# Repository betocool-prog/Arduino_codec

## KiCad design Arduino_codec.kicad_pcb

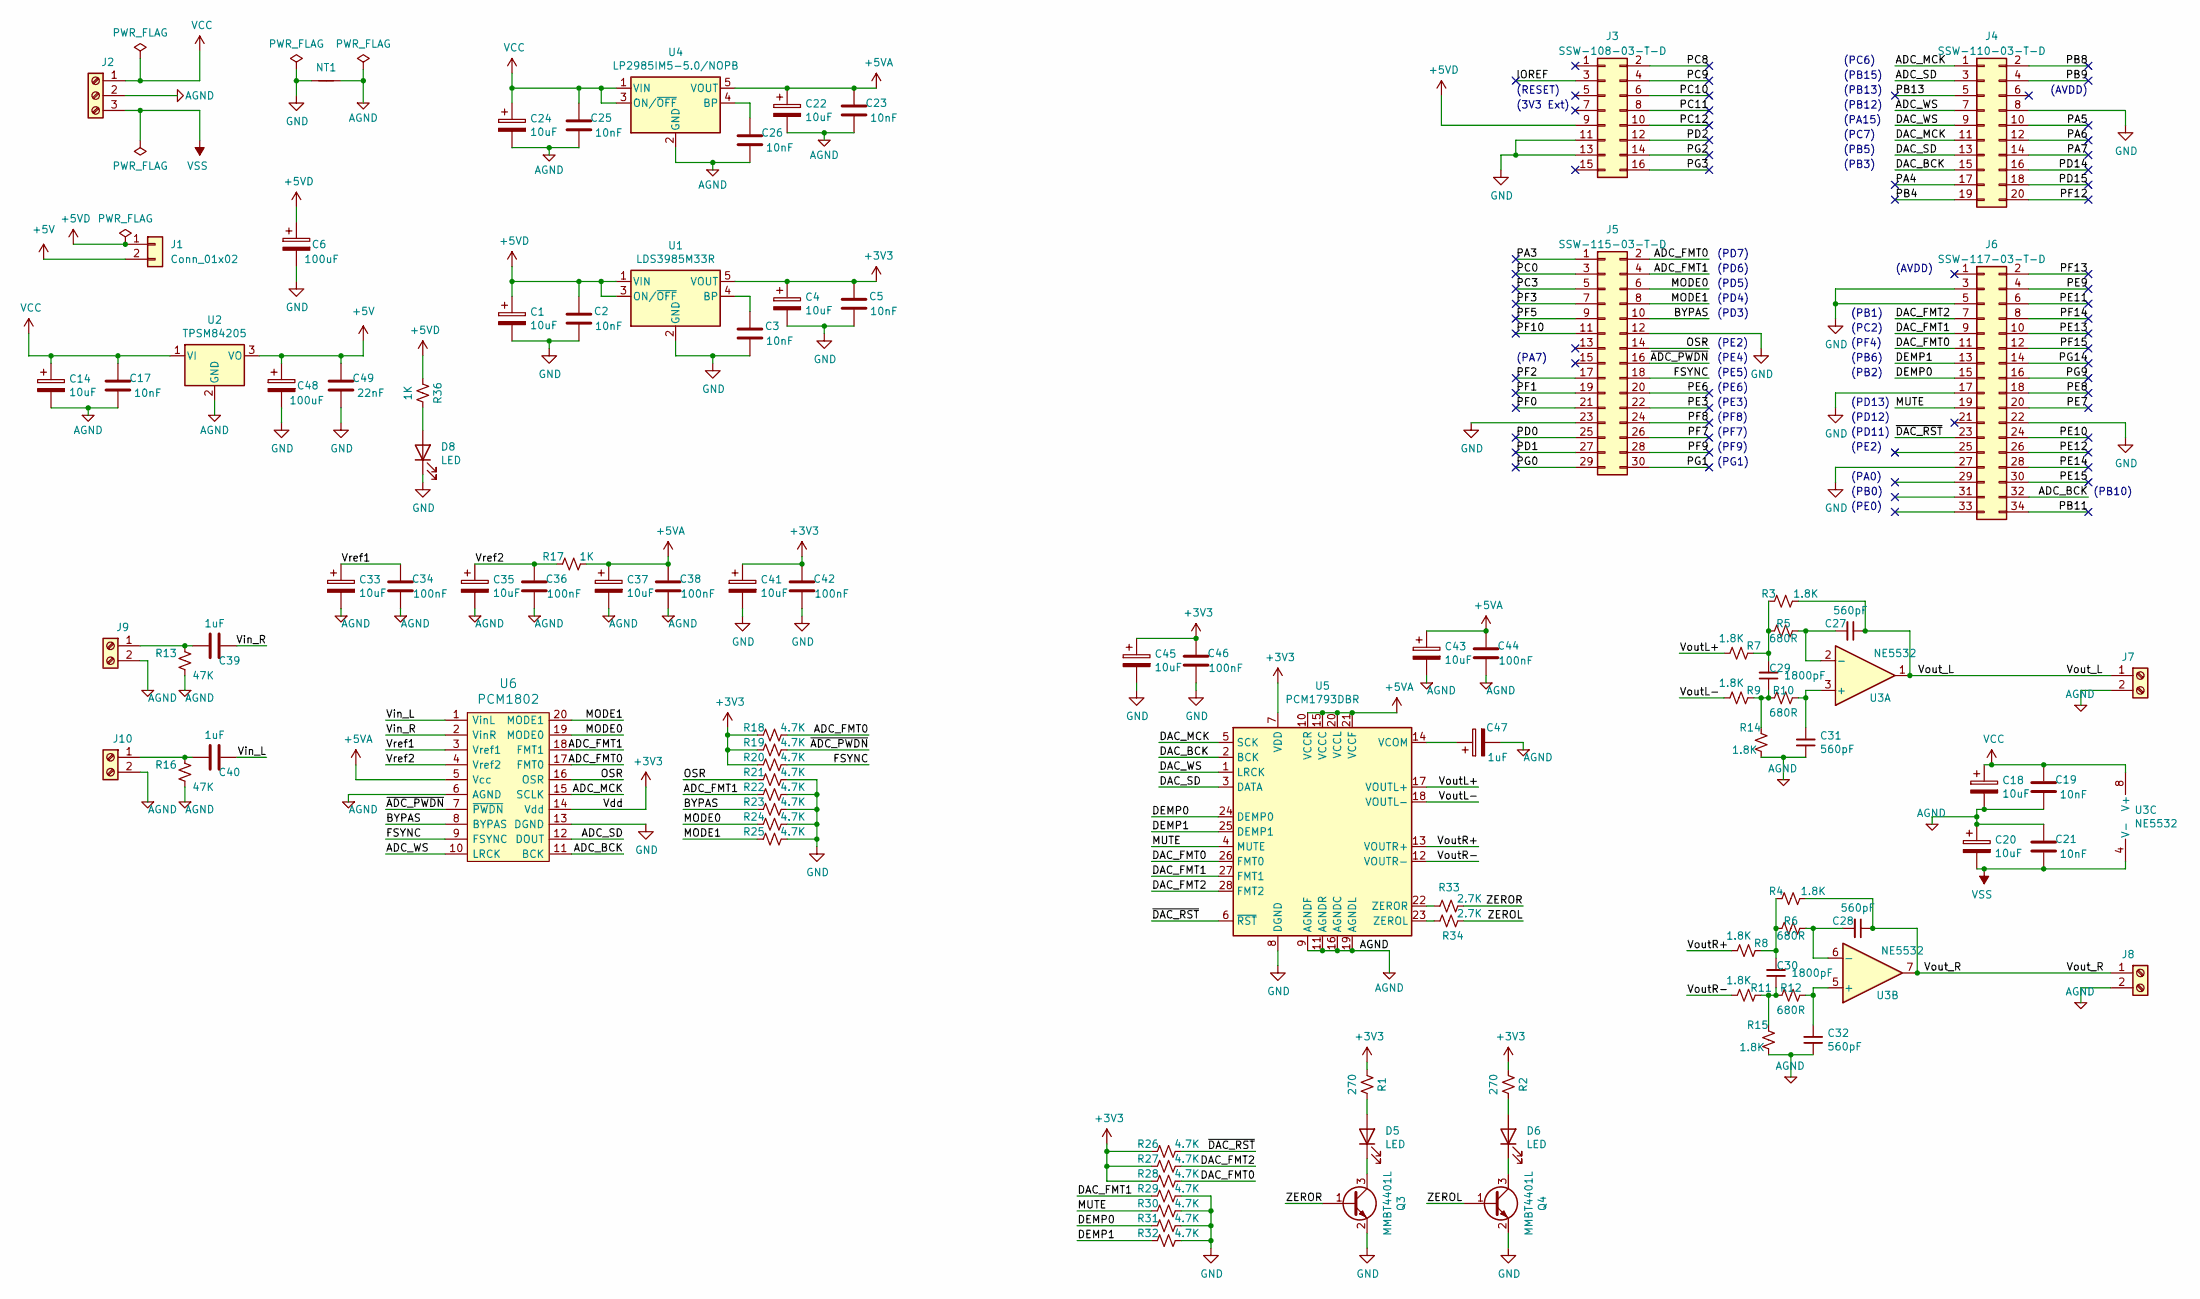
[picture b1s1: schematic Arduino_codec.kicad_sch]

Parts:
C1, C4, C14, C18, C20, C22, C24: 10uF; CP_EIA-6032-20_AVX-F_Pad2.25x2.35mm_HandSolder; Part # TRJC106K035R0600
C2, C3, C5: 10nF; C_0603_1608Metric_Pad1.08x0.95mm_HandSolder; Part # C0603C103M5RACTU
C6, C48: 100uF; CP_EIA-7343-30_AVX-N_Pad2.25x2.55mm_HandSolder; Part # TPSD107M010R0050
C17, C19, C21, C23, C25, C26: 10nF; C_0603_1608Metric_Pad1.05x0.95mm_HandSolder; Part # C0603C103M5RACTU
C27, C28, C31, C32: 560pF; C_0603_1608Metric_Pad1.05x0.95mm_HandSolder
C29, C30: 1800pF; C_0603_1608Metric_Pad1.05x0.95mm_HandSolder
C33, C35, C37, C41, C43, C45: 10uF; CP_EIA-2012-15_AVX-P_Pad1.30x1.05mm_HandSolder; Part # TLJR106M010R2000
C34, C36, C38, C42, C44, C46: 100nF; C_0603_1608Metric_Pad1.05x0.95mm_HandSolder; Part # C0603C103M5RACTU
C39, C40: 1uF; C_1210_3225Metric_Pad1.42x2.65mm_HandSolder; Part # ECP-U1C105MA5
C47: 1uF; CP_EIA-2012-15_AVX-P_Pad1.30x1.05mm_HandSolder; Part # TPSR105K010R9000
C49: 22nF; C_0603_1608Metric_Pad1.05x0.95mm_HandSolder; Part # C0603C223M5RAC7867
D5, D6, D8: LED; LED_0603_1608Metric_Pad1.05x0.95mm_HandSolder; Part # LT Q39G-Q1OO-25-1
J1: Conn_01x02; PinHeader_1x02_P2.54mm_Vertical
J2: Screw_Terminal_01x03; TerminalBlock_Phoenix_MPT-0,5-3-2.54_1x03_P2.54mm_Horizontal; Part # 1725669
J3: Conn_02x08_Odd_Even; PinHeader_2x08_P2.54mm_Vertical; Part # SSW-108-03-T-D
J4: Conn_02x10_Odd_Even; PinHeader_2x10_P2.54mm_Vertical; Part # SSW-110-03-T-D
J5: Conn_02x15_Odd_Even; PinHeader_2x15_P2.54mm_Vertical; Part # SSW-115-03-T-D
J6: Conn_02x17_Odd_Even; PinHeader_2x17_P2.54mm_Vertical; Part # SSW-117-03-T-D
J7, J8, J9, J10: Screw_Terminal_01x02; TerminalBlock_Phoenix_MPT-0,5-2-2.54_1x02_P2.54mm_Horizontal; Part # 1725656
NT1: Net-Tie_2; NetTie-2_SMD_Pad2.0mm
Q3, Q4: MMBT4401L; SOT-23; Part # MMBT4401L
R1, R2: 270; R_0603_1608Metric_Pad0.98x0.95mm_HandSolder
R3, R4, R7, R8, R9, R11, R14, R15: 1.8K; R_0603_1608Metric_Pad1.05x0.95mm_HandSolder
R5, R6, R10, R12: 680R; R_0603_1608Metric_Pad1.05x0.95mm_HandSolder
R13, R16: 47K; R_0603_1608Metric_Pad1.05x0.95mm_HandSolder
R17, R36: 1K; R_0603_1608Metric_Pad1.05x0.95mm_HandSolder
R18, R19, R20, R21, R22, R23, R24, R25, R26, R27, R28, R29, R30, R31, R32: 4.7K; R_0603_1608Metric_Pad1.05x0.95mm_HandSolder
R33, R34: 2.7K; R_0603_1608Metric_Pad1.05x0.95mm_HandSolder
U1: LDS3985M33R; SOT-23-5_HandSoldering; Part # LDS3985M33R
U2: TPSM84205; TO-220-3_Vertical
U3: NE5532; SOIC-8_3.9x4.9mm_P1.27mm; Part # NE5532DR
U4: LP2985IM5-5.0/NOPB; SOT-23-5_HandSoldering; Part # LP2985IM5-5.0/NOPB
U5: PCM1793DBR; SSOP-28_5.3x10.2mm_P0.65mm; Part # PCM1793DBR
U6: PCM1802; SSOP-20_5.3x7.2mm_P0.65mm; Part # PCM1802DBR

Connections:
+3V3: C4.1, C5.1, C41.1, C42.1, C45.1, C46.1, R1.2, R2.2, R18.1, R19.1, R20.1, R26.1, R27.1, R28.1, U1.5 (VOUT), U5.7 (VDD), U6.14 (Vdd)
+5V: C48.1, C49.1, J1.2, U2.3 (VO)
+5VA: C22.1, C23.1, C37.1, C38.1, C43.1, C44.1, R17.2, U4.5 (VOUT), U5.10 (VCCR), U5.15 (VCCC), U5.20 (VCCL), U5.21 (VCCF), U6.5 (Vcc)
+5VD: C1.1, C2.1, C6.1, J1.1, J3.9, R36.2, U1.1 (VIN), U1.3 (ON/~OFF)
/ADC_BCK: J6.32, U6.11 (BCK)
/ADC_FMT0: J5.2, R18.2, U6.17 (FMT0)
/ADC_FMT1: J5.4, R22.1, U6.18 (FMT1)
/ADC_MCK: J4.1, U6.15 (SCLK)
/ADC_SD: J4.3, U6.12 (DOUT)
/ADC_WS: J4.7, U6.10 (LRCK)
/BYPAS: J5.10, R23.1, U6.8 (BYPAS)
/DAC_BCK: J4.15, U5.2 (BCK)
/DAC_FMT0: J6.11, R28.2, U5.26 (FMT0)
/DAC_FMT1: J6.9, R29.1, U5.27 (FMT1)
/DAC_FMT2: J6.7, R27.2, U5.28 (FMT2)
/DAC_MCK: J4.11, U5.5 (SCK)
/DAC_SD: J4.13, U5.3 (DATA)
/DAC_WS: J4.9, U5.1 (LRCK)
/DEMP0: J6.15, R31.1, U5.24 (DEMP0)
/DEMP1: J6.13, R32.1, U5.25 (DEMP1)
/FSYNC: J5.18, R20.2, U6.9 (FSYNC)
/IOREF: J3.3
/MODE0: J5.6, R24.1, U6.19 (MODE0)
/MODE1: J5.8, R25.1, U6.20 (MODE1)
/MUTE: J6.19, R30.1, U5.4 (MUTE)
/OSR: J5.14, R21.1, U6.16 (OSR)
/PA3: J5.1
/PA4: J4.17
/PA5: J4.10
/PA6: J4.12
/PA7: J4.14
/PB4: J4.19
/PB8: J4.2
/PB9: J4.4
/PB11: J6.34
/PB13: J4.5
/PC0: J5.3
/PC3: J5.5
/PC8: J3.2
/PC9: J3.4
/PC10: J3.6
/PC11: J3.8
/PC12: J3.10
/PD0: J5.25
/PD1: J5.27
/PD2: J3.12
/PD14: J4.16
/PD15: J4.18
/PE3: J5.22
/PE6: J5.20
/PE7: J6.20
/PE8: J6.18
/PE9: J6.4
/PE10: J6.24
/PE11: J6.6
/PE12: J6.26
/PE13: J6.10
/PE14: J6.28
/PE15: J6.30
/PF0: J5.21
/PF1: J5.19
/PF2: J5.17
/PF3: J5.7
/PF5: J5.9
/PF7: J5.26
/PF8: J5.24
/PF9: J5.28
/PF10: J5.11
/PF12: J4.20
/PF13: J6.2
/PF14: J6.8
/PF15: J6.12
/PG0: J5.29
/PG1: J5.30
/PG2: J3.14
/PG3: J3.16
/PG9: J6.16
/PG14: J6.14
/Vin_L: C40.1, U6.1 (VinL)
/Vin_R: C39.1, U6.2 (VinR)
/VoutL+: R7.2, U5.17 (VOUTL+)
/VoutL-: R9.2, U5.18 (VOUTL-)
/VoutR+: R8.2, U5.13 (VOUTR+)
/VoutR-: R11.2, U5.12 (VOUTR-)
/Vout_L: C27.1, J7.1, R3.1, U3.1
/Vout_R: C28.1, J8.1, R4.1, U3.7
/Vref1: C33.1, C34.1, U6.3 (Vref1)
/Vref2: C35.1, C36.1, R17.1, U6.4 (Vref2)
/ZEROL: Q4.1 (B), R34.2
/ZEROR: Q3.1 (B), R33.2
/~ADC_PWDN: J5.16, R19.2, U6.7 (~PWDN)
/~DAC_RST: J6.23, R26.2, U5.6 (~RST)
AGND: C14.2, C17.2, C18.2, C19.2, C20.1, C21.1, C22.2, C23.2, C24.2, C25.2, C26.2, C31.1, C32.1, C33.2, C34.2, C35.2, C36.2, C37.2, C38.2, C43.2, C44.2, C47.2, J2.2, J7.2, J8.2, J9.2, J10.2, NT1.2, R13.2, R14.1, R15.1, R16.2, U2.2 (GND), U4.2 (GND), U5.9 (AGNDF), U5.11 (AGNDR), U5.16 (AGNDC), U5.19 (AGNDL), U6.6 (AGND)
GND: C1.2, C2.2, C3.2, C4.2, C5.2, C6.2, C41.2, C42.2, C45.2, C46.2, C48.2, C49.2, D8.1 (K), J3.11, J3.13, J4.8, J5.12, J5.23, J6.3, J6.5, J6.17, J6.22, J6.27, NT1.1, Q3.2 (E), Q4.2 (E), R21.2, R22.2, R23.2, R24.2, R25.2, R29.2, R30.2, R31.2, R32.2, U1.2 (GND), U5.8 (DGND), U6.13 (DGND)
unnamed: C3.1, U1.4 (BP)
unnamed: C26.1, U4.4 (BP)
unnamed: C27.2, R5.1, U3.2 (-)
unnamed: C28.2, R6.1, U3.6 (-)
unnamed: C29.1, R9.1, R10.2, R14.2
unnamed: C29.2, R3.2, R5.2, R7.1
unnamed: C30.1, R11.1, R12.2, R15.2
unnamed: C30.2, R4.2, R6.2, R8.1
unnamed: C31.2, R10.1, U3.3 (+)
unnamed: C32.2, R12.1, U3.5 (+)
unnamed: C39.2, J9.1, R13.1
unnamed: C40.2, J10.1, R16.1
unnamed: C47.1, U5.14 (VCOM)
unnamed: D5.1 (K), Q3.3 (C)
unnamed: D5.2 (A), R1.1
unnamed: D6.1 (K), Q4.3 (C)
unnamed: D6.2 (A), R2.1
unnamed: D8.2 (A), R36.1
unnamed: R33.1, U5.22 (ZEROR)
unnamed: R34.1, U5.23 (ZEROL)
VCC: C14.1, C17.1, C18.1, C19.1, C24.1, C25.1, J2.1, U2.1 (VI), U3.8 (V+), U4.1 (VIN), U4.3 (ON/~OFF)
VSS: C20.2, C21.2, J2.3, U3.4 (V-)

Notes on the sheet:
(PD11)
(PA7)
(PE5)
(PD13)
(RESET)
(PF9)
(PE0)
(AVDD)
(PE6)
(PD12)
(PE3)
(PB3)
(PD6)
(PE2)
(PB13)
(PE4)
(PF7)
(PB2)
(PB6)
(PB15)
(PC6)
(PG1)
(PD4)
(PB0)
(PD3)
(PA0)
(PF4)
(PA15)
(PD5)
(PF8)
(PB10)
(PB1)
(PC7)
(PC2)
(3V3 Ext)
(PB5)
(PD7)
(PB12)

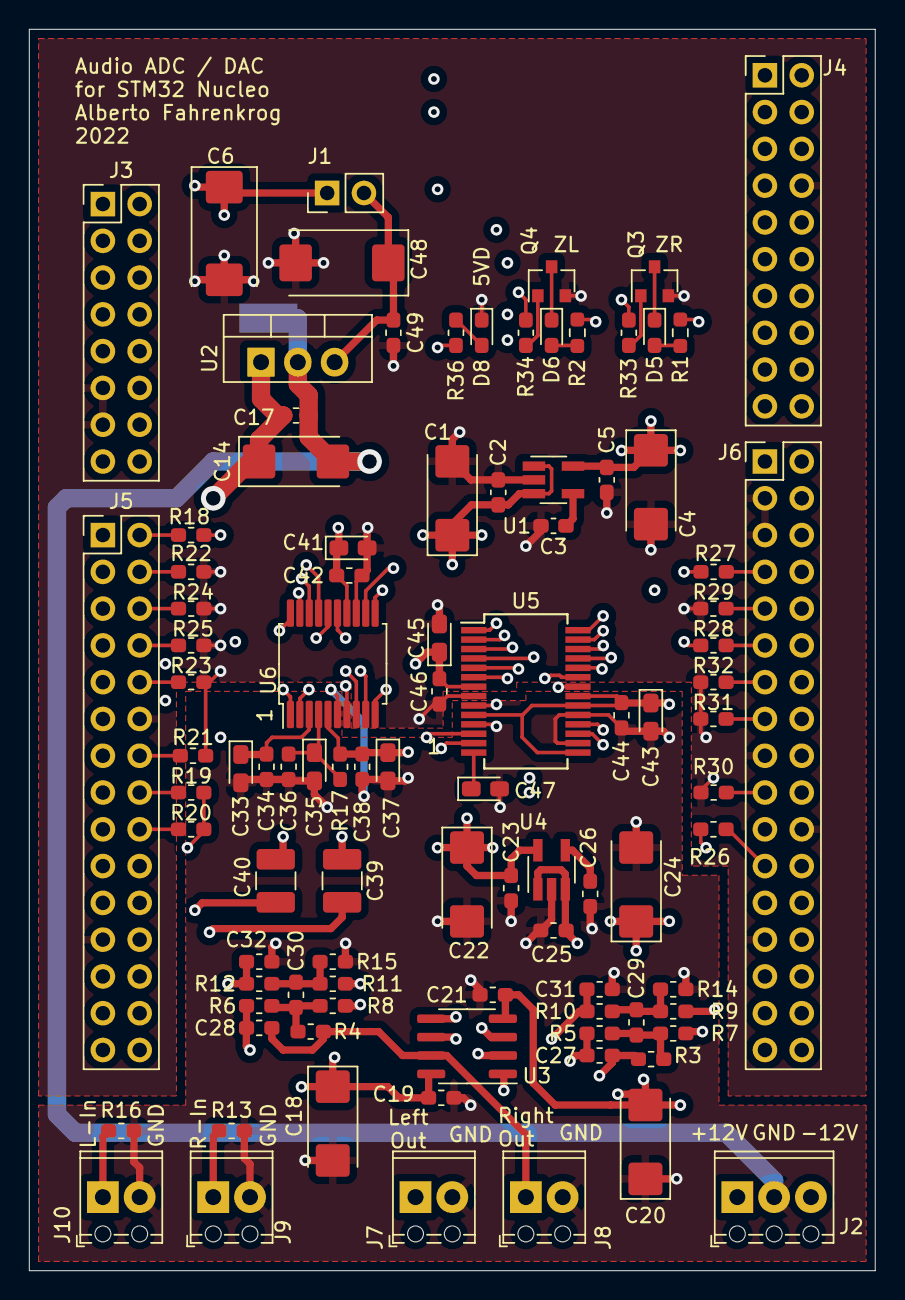
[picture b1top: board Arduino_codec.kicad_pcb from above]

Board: 4 copper layers, 58.4 x 85.7 mm, 97 parts (1 on the bottom side), 63 nets.

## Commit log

2022-01-30 1st review before fabrication
    Ready to review before fabrication outputs.
2024-02-19 Simplified branch
